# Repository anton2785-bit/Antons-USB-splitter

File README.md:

# Antons-USB-splitter 
---
## What is this project

* This is a small PCB that can take 1 input signal via USB A and output 4 separate USB A signals.  
---
## Why i made this project

* I made the USB splitter because I want to have a USB hub closer to my keyboard or me in general so that I dont have to dive behind my  PC to plug a USB.

  ---
  ## Images
  * This is an image of the schematic:
  * 
  * This is the PCB:
  * 

  * The 3D model of the PCB:
  * 

  ---
  
  ## Assembly
  * First you need to soulder all of the capacitors (I think 5), the fuses ( 5 of them) and the crystal.
  * Then you can soulder the bigger components like the chip and the USB ports.
  * Thats it.
 ## BOM
 
| Component | Purpose | Qty | Cost (USD) | Distributor |
|-----------|---------|-----|------------|-------------|
| Capacitors 100nF | Decoupling | 1 lot | $1.90 | [AliExpress](https://www.aliexpress.com/item/1005007470747384.html) |
| Crystal 12MHz | Clock source | 1 lot | $1.80 | [AliExpress](https://www.aliexpress.com/item/1005006126635124.html) |
| USB Connectors | Signal in/out | 1 lot | $4.08 | [AliExpress](https://www.aliexpress.com/item/1005006092828018.html) |
| Polyfuses | Overcurrent protection | 1 lot | $4.01 | [AliExpress](https://www.aliexpress.com/item/32918666236.html) |
| Capacitors many values | Decoupling | 1 lot | $4.31 | [AliExpress](https://www.aliexpress.com/item/1005006157020955.html) |
| PCB | Board fabrication | 1 | $4.20 | JLCPCB |
| **Total** | | | **$20.30** | |
---
## Credits

* Designed and built by *(Anton/ Anton-2785-bit)
* Inspired by open‑source mechanical keyboard and hackpad communities (https://macondo.hackclub.com/).

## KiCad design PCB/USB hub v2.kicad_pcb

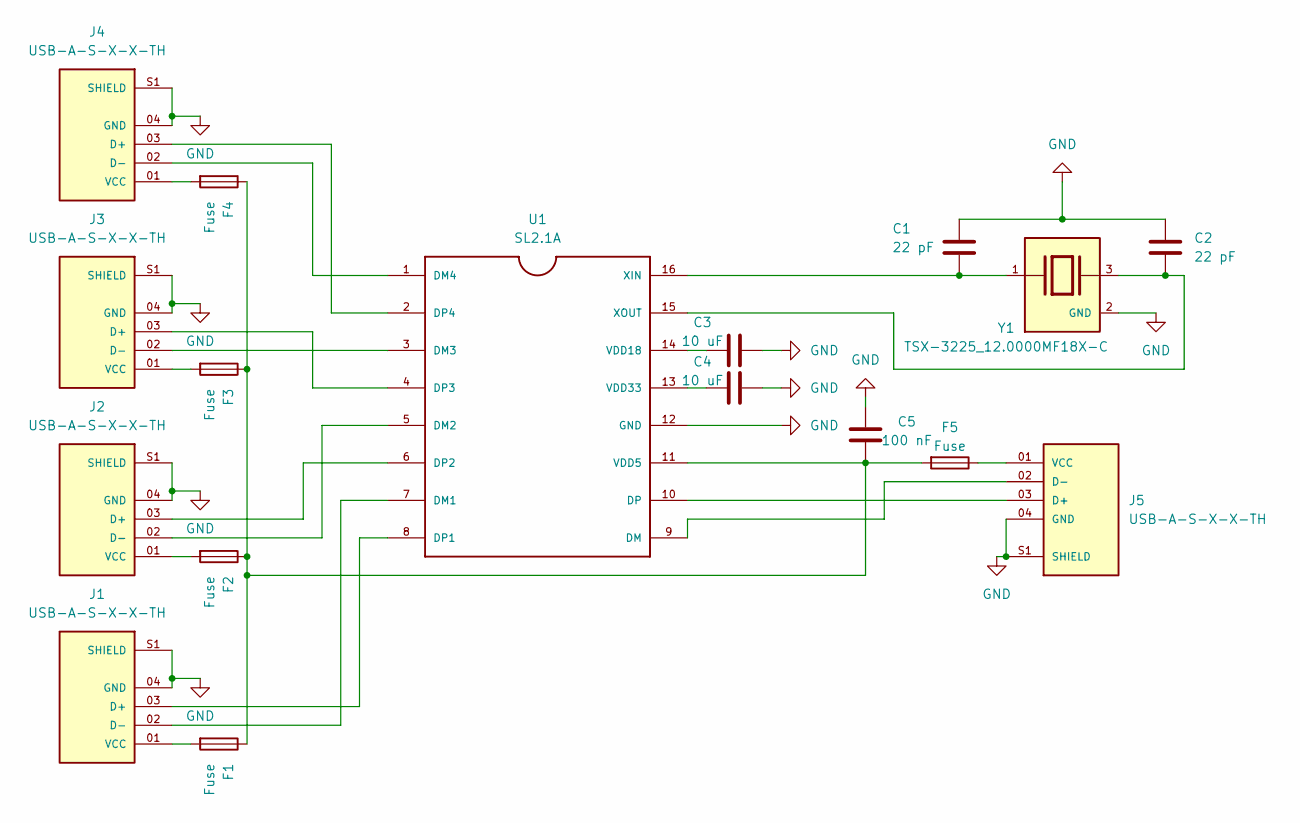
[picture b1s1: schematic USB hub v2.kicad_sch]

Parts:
C1, C2: 22 pF; C_0805_2012Metric_Pad1.18x1.45mm_HandSolder
C3, C4: 10 uF; C_0805_2012Metric_Pad1.18x1.45mm_HandSolder
C5: 100 nF; C_0805_2012Metric_Pad1.18x1.45mm_HandSolder
F1, F2, F3, F4, F5: Fuse; Fuse_0805_2012Metric_Pad1.15x1.40mm_HandSolder
J1, J2, J3, J4, J5: USB-A-S-X-X-TH; SAMTEC_USB-A-S-X-X-TH; PARTREV R
U1: SL2.1A; SO16
Y1: TSX-3225_12.0000MF18X-C; Crystal_SMD_SeikoEpson_TSX3225-4Pin_3.2x2.5mm_HandSoldering; PARTREV N/A

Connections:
GND: C1.1, C2.1, C3.2, C4.2, C5.1, J1.04 (GND), J1.S1 (SHIELD), J1.S2 (SHIELD), J2.04 (GND), J2.S1 (SHIELD), J2.S2 (SHIELD), J3.04 (GND), J3.S1 (SHIELD), J3.S2 (SHIELD), J4.04 (GND), J4.S1 (SHIELD), J4.S2 (SHIELD), J5.04 (GND), J5.S1 (SHIELD), J5.S2 (SHIELD), U1.12 (GND), Y1.2 (GND), Y1.4 (GND)
unnamed: J1.03 (D+), U1.8 (DP1)
unnamed: J1.02 (D-), U1.7 (DM1)
unnamed: F1.2, J1.01 (VCC)
unnamed: J2.03 (D+), U1.6 (DP2)
unnamed: J2.02 (D-), U1.5 (DM2)
unnamed: F2.2, J2.01 (VCC)
unnamed: J3.03 (D+), U1.4 (DP3)
unnamed: J3.02 (D-), U1.3 (DM3)
unnamed: F3.2, J3.01 (VCC)
unnamed: J4.03 (D+), U1.2 (DP4)
unnamed: J4.02 (D-), U1.1 (DM4)
unnamed: F4.2, J4.01 (VCC)
unnamed: J5.03 (D+), U1.10 (DP)
unnamed: J5.02 (D-), U1.9 (DM)
unnamed: F5.1, J5.01 (VCC)
unnamed: C5.2, F1.1, F2.1, F3.1, F4.1, F5.2, U1.11 (VDD5)
unnamed: C3.1, U1.14 (VDD18)
unnamed: C4.1, U1.13 (VDD33)
unnamed: C1.2, U1.16 (XIN), Y1.1
unnamed: C2.2, U1.15 (XOUT), Y1.3

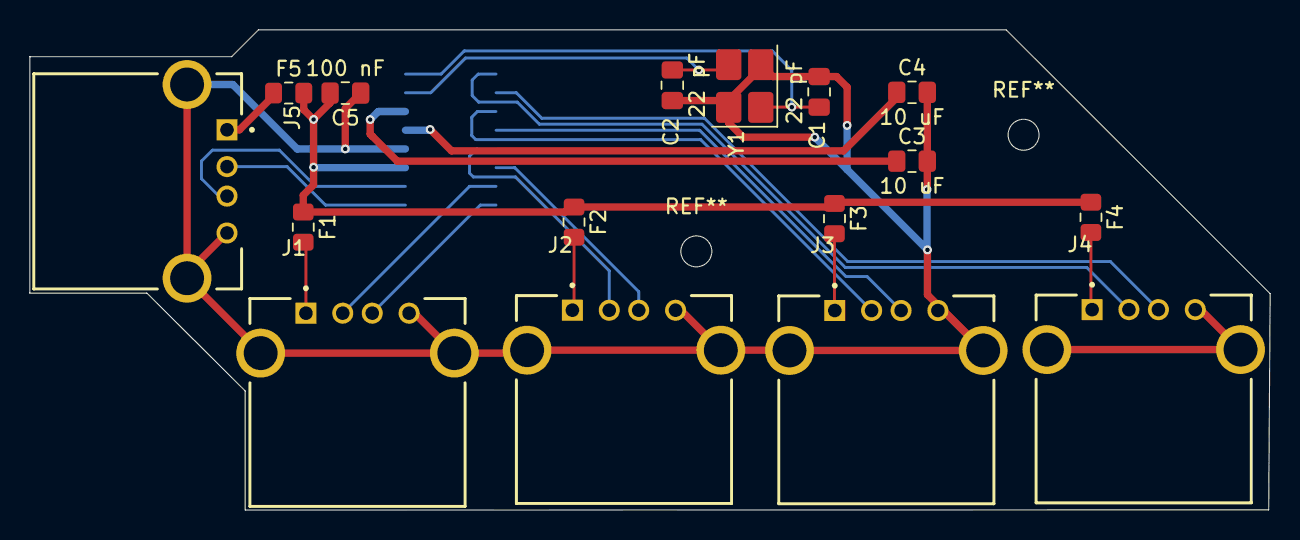
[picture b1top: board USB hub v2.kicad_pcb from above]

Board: 2 copper layers, 84.2 x 32.6 mm, 17 parts (1 on the bottom side), 21 nets.

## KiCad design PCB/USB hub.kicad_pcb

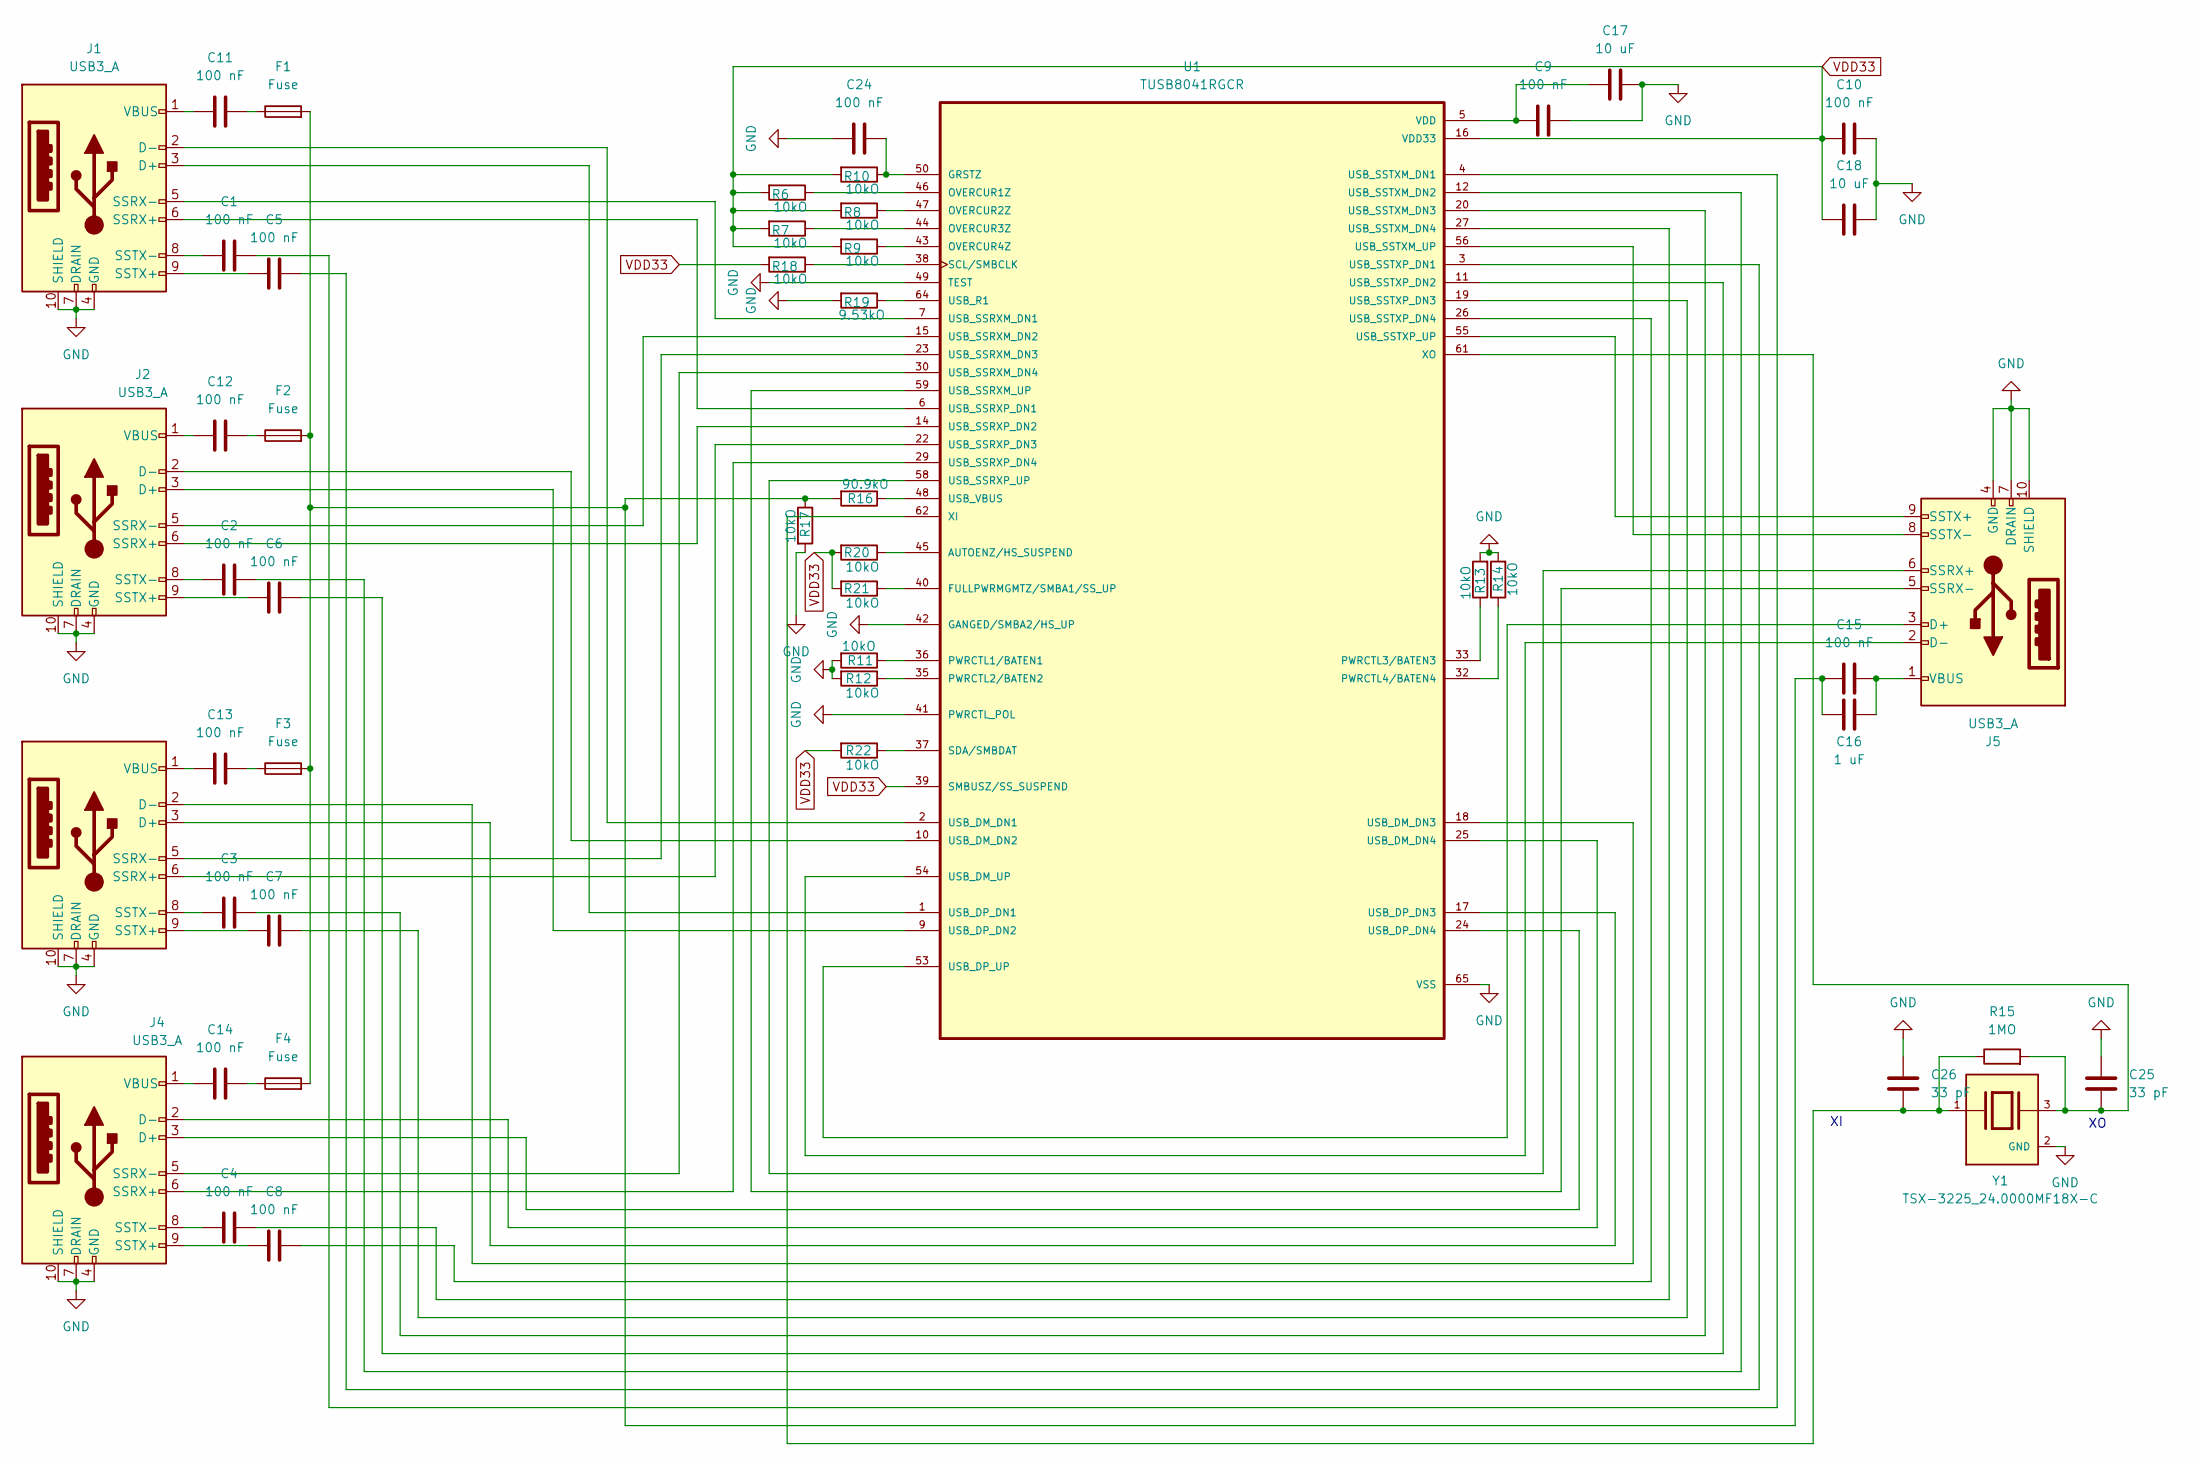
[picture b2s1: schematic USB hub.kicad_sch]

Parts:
C1, C2, C3, C4, C5, C6, C7, C8, C9, C10, C11, C12, C13, C14, C15, C24: 100 nF; C_0805_2012Metric_Pad1.18x1.45mm_HandSolder
C16: 1 uF; C_0805_2012Metric_Pad1.18x1.45mm_HandSolder
C17, C18: 10 uF; C_0805_2012Metric_Pad1.18x1.45mm_HandSolder
C25, C26: 33 pF; C_0805_2012Metric_Pad1.18x1.45mm_HandSolder
F1, F2, F3, F4: Fuse; L_0805_2012Metric_Pad1.05x1.20mm_HandSolder
J1, J2, J3, J4, J5: USB3_A; CONN_1932258-1
R6, R7, R8, R9, R10, R11, R12, R13, R14, R17, R18, R20, R21, R22: 10kO; R_0805_2012Metric_Pad1.20x1.40mm_HandSolder
R15: 1MO; R_0805_2012Metric_Pad1.20x1.40mm_HandSolder
R16: 90.9kO; R_0805_2012Metric_Pad1.20x1.40mm_HandSolder
R19: 9.53kO; R_0805_2012Metric_Pad1.20x1.40mm_HandSolder
U1: TUSB8041RGCR; QFN50P900X900X100-65N
Y1: TSX-3225_24.0000MF18X-C; Crystal_SMD_SeikoEpson_TSX3225-4Pin_3.2x2.5mm_HandSoldering; PARTREV N/A

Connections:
GND: C9.1, C10.1, C17.1, C18.1, C24.2, C25.1, C26.1, J1.4 (GND), J1.7 (DRAIN), J1.10 (SHIELD), J2.4 (GND), J2.7 (DRAIN), J2.10 (SHIELD), J3.4 (GND), J3.7 (DRAIN), J3.10 (SHIELD), J4.4 (GND), J4.7 (DRAIN), J4.10 (SHIELD), J5.4 (GND), J5.7 (DRAIN), J5.10 (SHIELD), R11.2, R12.2, R13.2, R14.2, R17.2, R19.2, U1.41 (PWRCTL_POL), U1.42 (GANGED/SMBA2/HS_UP), U1.49 (TEST), U1.65 (VSS), Y1.2 (GND), Y1.4 (GND)
unnamed: C11.1, F1.1
unnamed: C12.1, F2.1
unnamed: C13.1, F3.1
unnamed: C14.1, F4.1
unnamed: C15.2, C16.2, F1.2, F2.2, F3.2, F4.2, R16.2, R17.1
unnamed: J1.3 (D+), U1.1 (USB_DP_DN1)
unnamed: J1.2 (D-), U1.2 (USB_DM_DN1)
unnamed: J1.6 (SSRX+), U1.6 (USB_SSRXP_DN1)
unnamed: J1.5 (SSRX-), U1.7 (USB_SSRXM_DN1)
unnamed: C5.2, J1.9 (SSTX+)
unnamed: C1.2, J1.8 (SSTX-)
unnamed: C11.2, J1.1 (VBUS)
unnamed: J2.3 (D+), U1.9 (USB_DP_DN2)
unnamed: J2.2 (D-), U1.10 (USB_DM_DN2)
unnamed: J2.6 (SSRX+), U1.14 (USB_SSRXP_DN2)
unnamed: J2.5 (SSRX-), U1.15 (USB_SSRXM_DN2)
unnamed: C6.2, J2.9 (SSTX+)
unnamed: C2.2, J2.8 (SSTX-)
unnamed: C12.2, J2.1 (VBUS)
unnamed: J3.3 (D+), U1.17 (USB_DP_DN3)
unnamed: J3.2 (D-), U1.18 (USB_DM_DN3)
unnamed: J3.6 (SSRX+), U1.22 (USB_SSRXP_DN3)
unnamed: J3.5 (SSRX-), U1.23 (USB_SSRXM_DN3)
unnamed: C7.2, J3.9 (SSTX+)
unnamed: C3.2, J3.8 (SSTX-)
unnamed: C13.2, J3.1 (VBUS)
unnamed: J4.3 (D+), U1.24 (USB_DP_DN4)
unnamed: J4.2 (D-), U1.25 (USB_DM_DN4)
unnamed: J4.6 (SSRX+), U1.29 (USB_SSRXP_DN4)
unnamed: J4.5 (SSRX-), U1.30 (USB_SSRXM_DN4)
unnamed: C8.2, J4.9 (SSTX+)
unnamed: C4.2, J4.8 (SSTX-)
unnamed: C14.2, J4.1 (VBUS)
unnamed: J5.3 (D+), U1.53 (USB_DP_UP)
unnamed: J5.2 (D-), U1.54 (USB_DM_UP)
unnamed: J5.6 (SSRX+), U1.58 (USB_SSRXP_UP)
unnamed: J5.5 (SSRX-), U1.59 (USB_SSRXM_UP)
unnamed: J5.9 (SSTX+), U1.55 (USB_SSTXP_UP)
unnamed: J5.8 (SSTX-), U1.56 (USB_SSTXM_UP)
unnamed: C15.1, C16.1, J5.1 (VBUS)
unnamed: R20.1, U1.45 (AUTOENZ/HS_SUSPEND)
unnamed: R21.1, U1.40 (FULLPWRMGMTZ/SMBA1/SS_UP)
unnamed: C24.1, R10.1, U1.50 (GRSTZ)
unnamed: R6.1, U1.46 (OVERCUR1Z)
unnamed: R8.1, U1.47 (OVERCUR2Z)
unnamed: R7.1, U1.44 (OVERCUR3Z)
unnamed: R9.1, U1.43 (OVERCUR4Z)
unnamed: R11.1, U1.36 (PWRCTL1/BATEN1)
unnamed: R12.1, U1.35 (PWRCTL2/BATEN2)
unnamed: R13.1, U1.33 (PWRCTL3/BATEN3)
unnamed: R14.1, U1.32 (PWRCTL4/BATEN4)
unnamed: R18.1, U1.38 (SCL/SMBCLK)
unnamed: R22.1, U1.37 (SDA/SMBDAT)
unnamed: R19.1, U1.64 (USB_R1)
unnamed: C1.1, U1.4 (USB_SSTXM_DN1)
unnamed: C2.1, U1.12 (USB_SSTXM_DN2)
unnamed: C3.1, U1.20 (USB_SSTXM_DN3)
unnamed: C4.1, U1.27 (USB_SSTXM_DN4)
unnamed: C5.1, U1.3 (USB_SSTXP_DN1)
unnamed: C6.1, U1.11 (USB_SSTXP_DN2)
unnamed: C7.1, U1.19 (USB_SSTXP_DN3)
unnamed: C8.1, U1.26 (USB_SSTXP_DN4)
unnamed: R16.1, U1.48 (USB_VBUS)
unnamed: C26.2, R15.1, U1.62 (XI), Y1.1
unnamed: C25.2, R15.2, U1.61 (XO), Y1.3
VDD: C9.2, C17.2, U1.5 (VDD), U1.8 (VDD), U1.13 (VDD), U1.21 (VDD), U1.28 (VDD), U1.31 (VDD), U1.51 (VDD), U1.57 (VDD)
VDD33: C10.2, C18.2, R6.2, R7.2, R8.2, R9.2, R10.2, R18.2, R20.2, R21.2, R22.2, U1.16 (VDD33), U1.34 (VDD33), U1.39 (SMBUSZ/SS_SUSPEND), U1.52 (VDD33), U1.63 (VDD33)

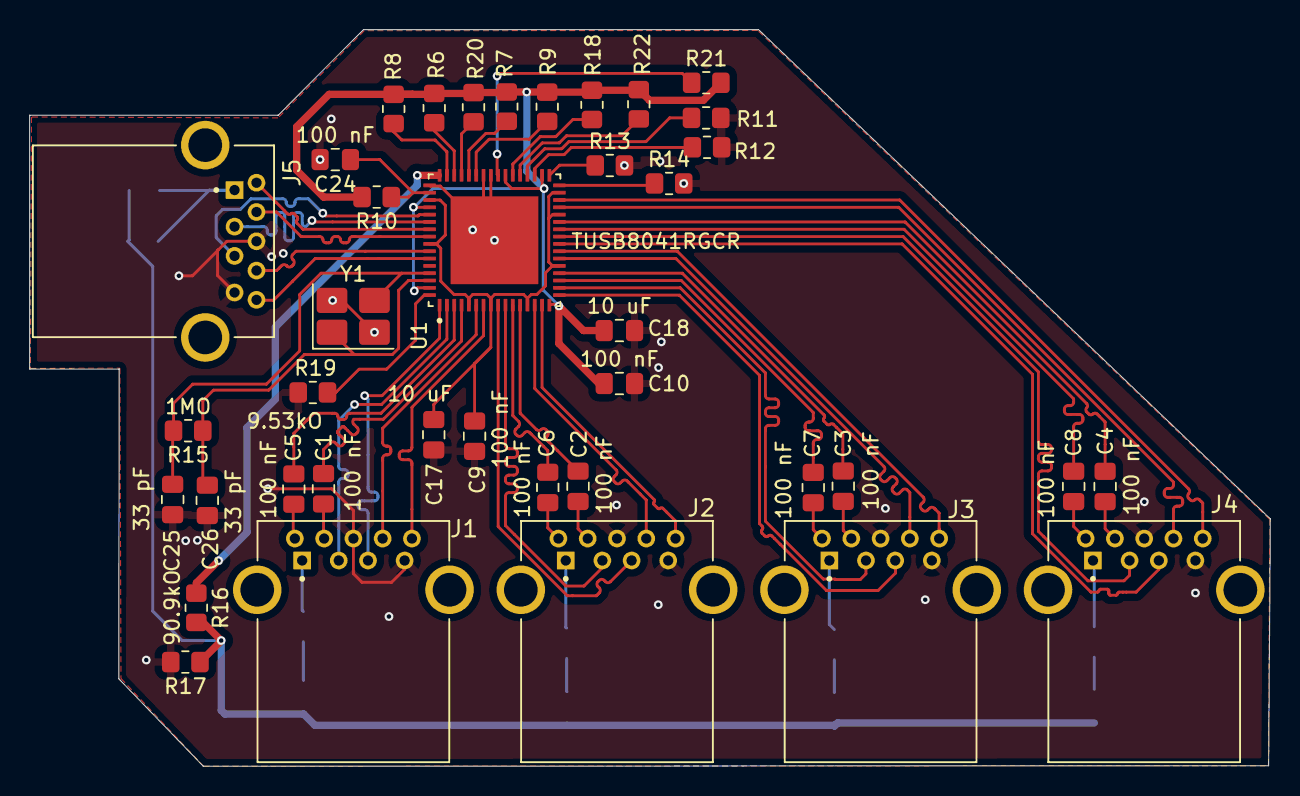
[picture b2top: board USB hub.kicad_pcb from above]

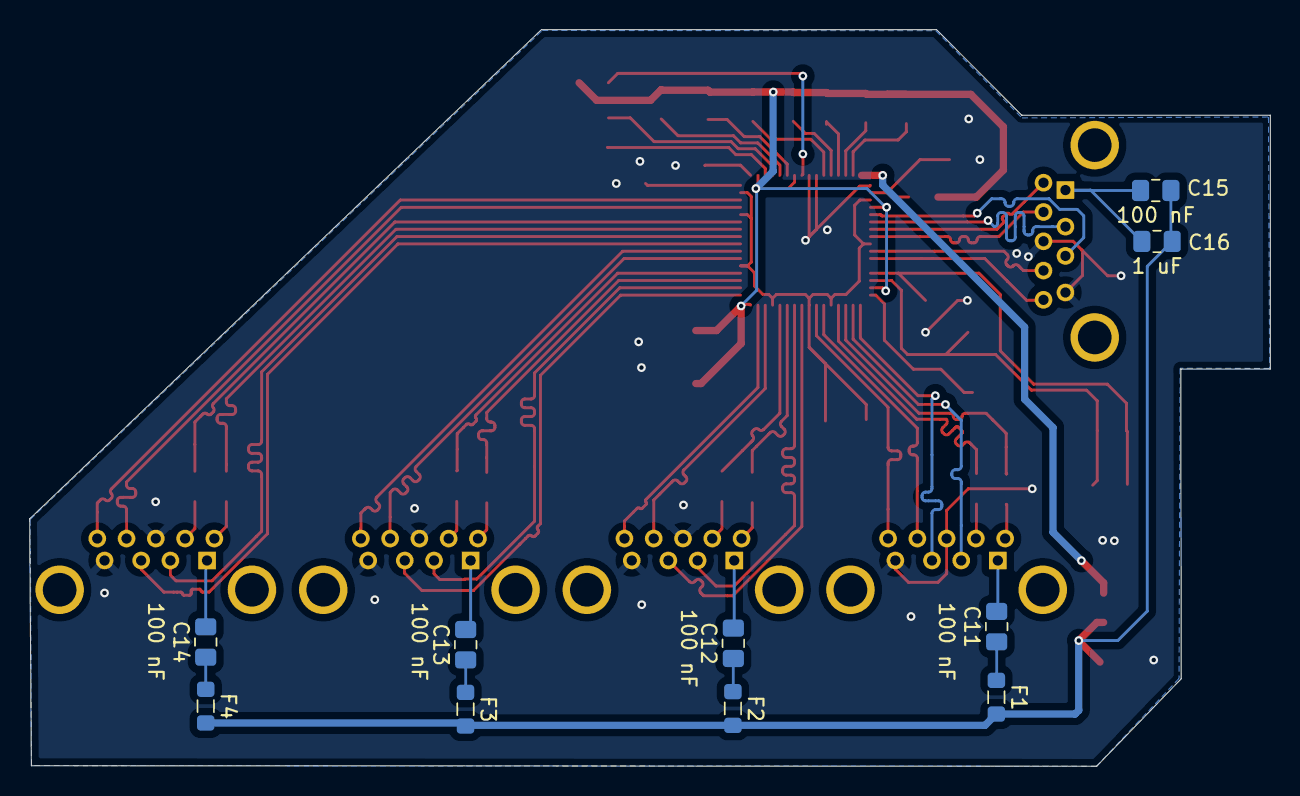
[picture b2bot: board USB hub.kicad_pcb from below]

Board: 2 copper layers, 84.8 x 50.3 mm, 49 parts (10 on the bottom side), 68 nets.

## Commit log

2026-04-07 File update
